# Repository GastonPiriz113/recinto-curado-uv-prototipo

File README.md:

# recinto-curado-uv-prototipo
Firmware y documentación del prototipo de recinto de curado

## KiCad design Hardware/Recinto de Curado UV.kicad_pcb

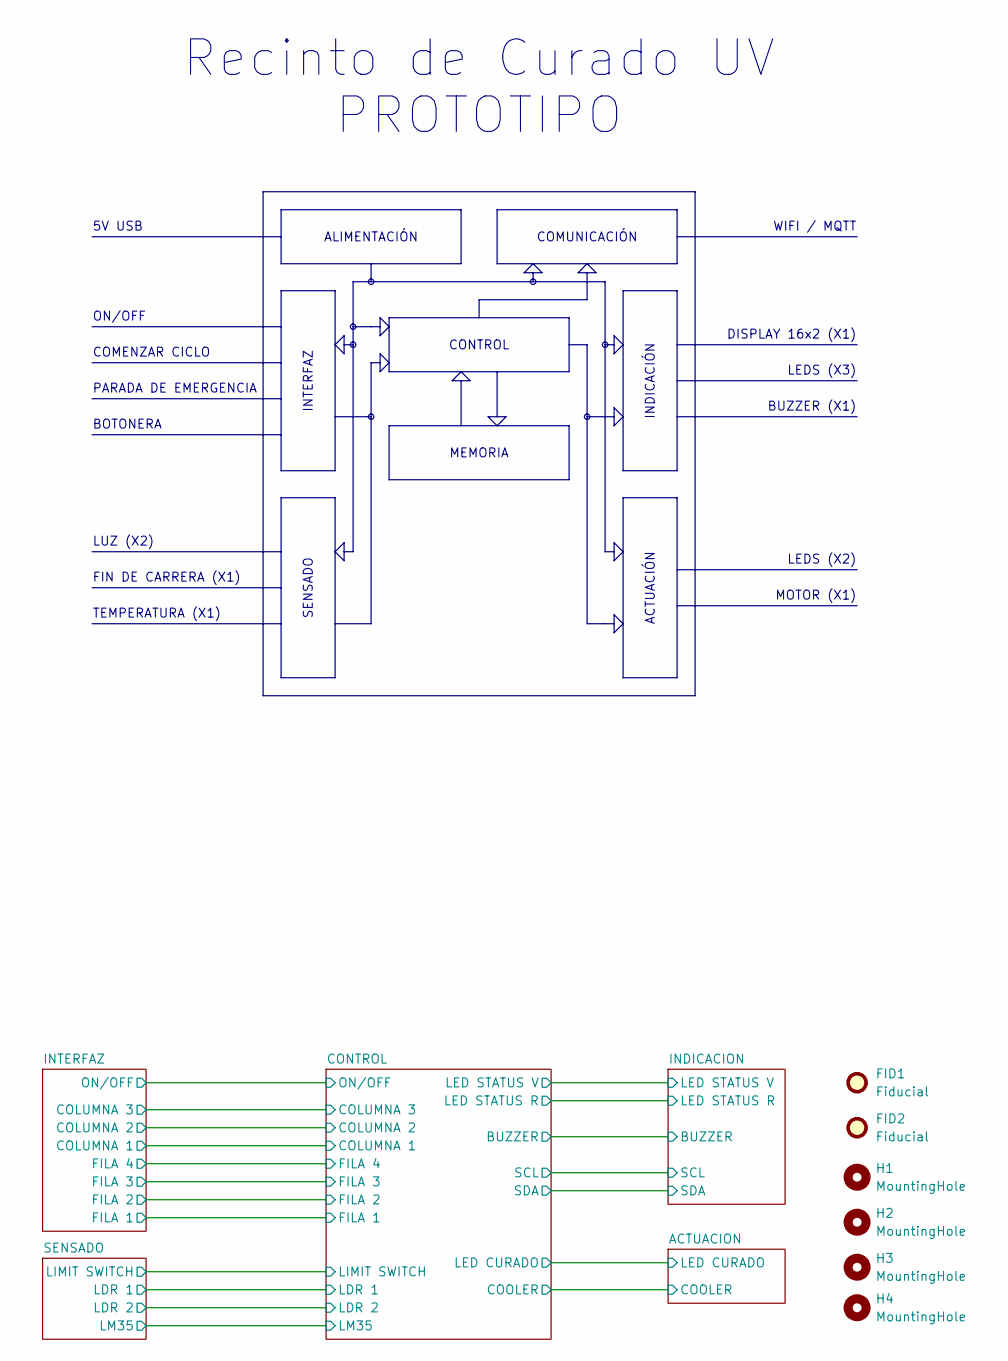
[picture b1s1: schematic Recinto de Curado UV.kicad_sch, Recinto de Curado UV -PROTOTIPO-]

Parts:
FID1, FID2: Fiducial; Fiducial_0.5mm_Mask1.5mm
H1, H2, H3, H4: MountingHole; MountingHole_3.2mm_M3_ISO7380

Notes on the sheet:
DISPLAY 16x2 (X1)
BUZZER (X1)
LEDS (X2)
ON/OFF
WIFI / MQTT
LUZ (X2)
PARADA DE EMERGENCIA
BOTONERA
MOTOR (X1)
COMENZAR CICLO
Recinto de Curado UV PROTOTIPO
LEDS (X3)
FIN DE CARRERA (X1)
5V USB
TEMPERATURA (X1)
MEMORIA
COMUNICACIÓN
SENSADO
INDICACIÓN
ALIMENTACIÓN
ACTUACIÓN
CONTROL
INTERFAZ

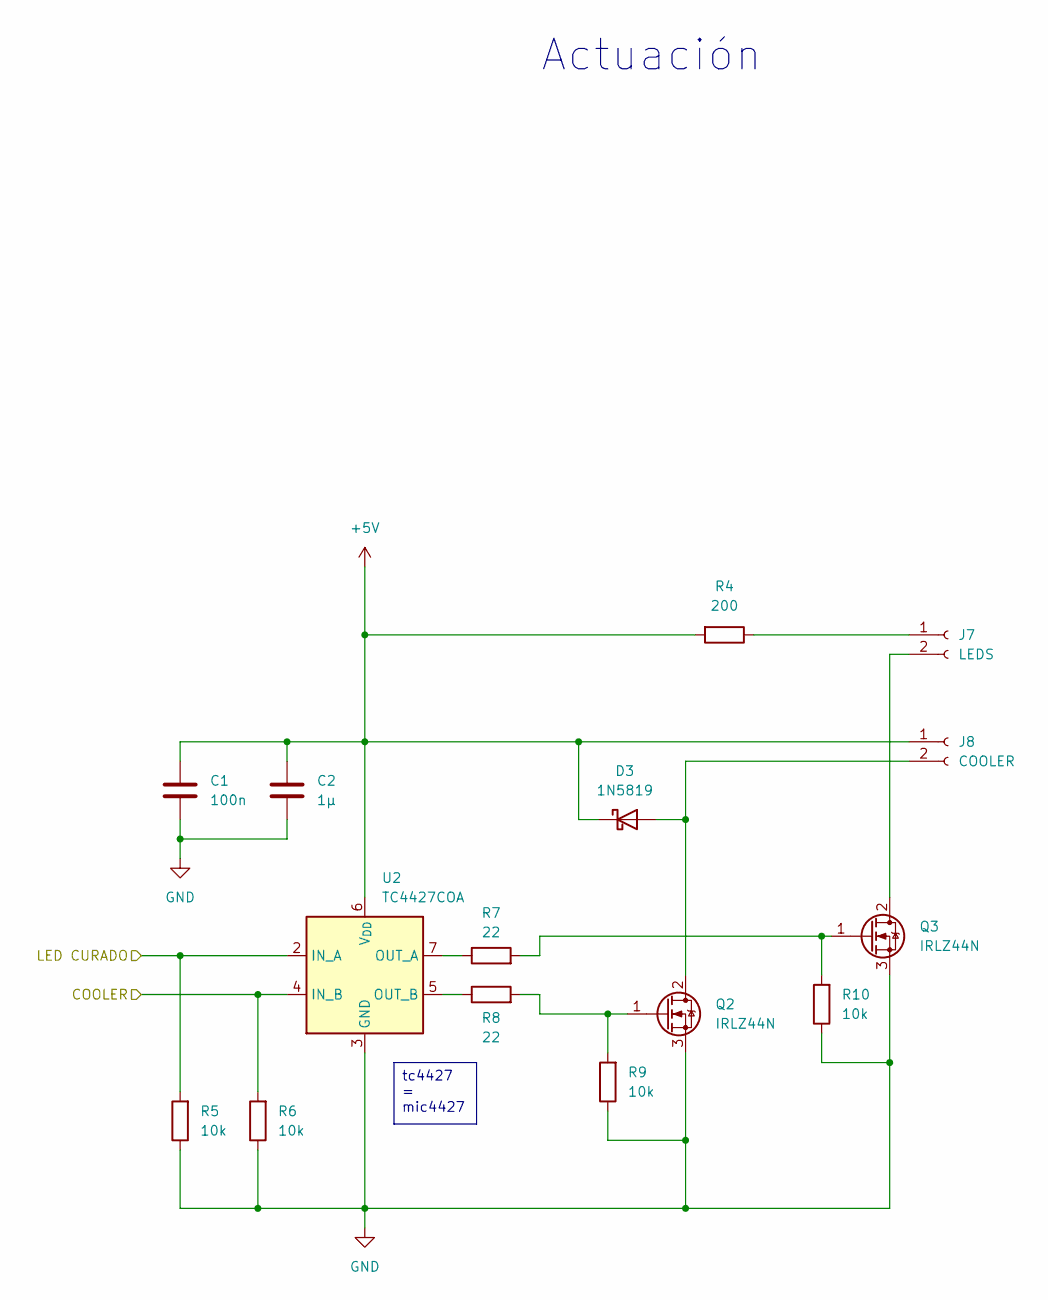
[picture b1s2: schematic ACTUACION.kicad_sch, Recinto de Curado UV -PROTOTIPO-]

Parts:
C1: 100n; C_Disc_D5.0mm_W2.5mm_P2.50mm
C2: 1µ; C_Disc_D5.0mm_W2.5mm_P2.50mm
D3: 1N5819; D_DO-41_SOD81_P10.16mm_Horizontal
J7: LEDS; PinHeader_1x02_P2.54mm_Vertical
J8: COOLER; PinHeader_1x02_P2.54mm_Vertical
Q2, Q3: IRLZ44N; TO-220-3_Horizontal_TabDown
R4: 200; R_Axial_DIN0207_L6.3mm_D2.5mm_P7.62mm_Horizontal
R5, R6, R9, R10: 10k; R_Axial_DIN0207_L6.3mm_D2.5mm_P7.62mm_Horizontal
R7, R8: 22; R_Axial_DIN0207_L6.3mm_D2.5mm_P7.62mm_Horizontal
U2: TC4427COA; SOIC-8_3.9x4.9mm_P1.27mm

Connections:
+5V: C1.1, C2.1, D3.1 (K), J8.1, R4.2, U2.6 (V_{DD}); also elsewhere on the board
/PROTOTIPO/ACTUACION/COOLER: R6.2, U2.4 (IN_B); also elsewhere on the board
/PROTOTIPO/ACTUACION/LED CURADO: R5.2, U2.2 (IN_A); also elsewhere on the board
GND: C1.2, C2.2, Q2.3 (S), Q3.3 (S), R5.1, R6.1, R9.1, R10.1, U2.3 (GND); also elsewhere on the board
unnamed: D3.2 (A), J8.2, Q2.2 (D)
unnamed: J7.1, R4.1
unnamed: J7.2, Q3.2 (D)
unnamed: Q2.1 (G), R8.2, R9.2
unnamed: Q3.1 (G), R7.2, R10.2
unnamed: R7.1, U2.7 (OUT_A)
unnamed: R8.1, U2.5 (OUT_B)

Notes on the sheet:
Actuación
tc4427 = mic4427

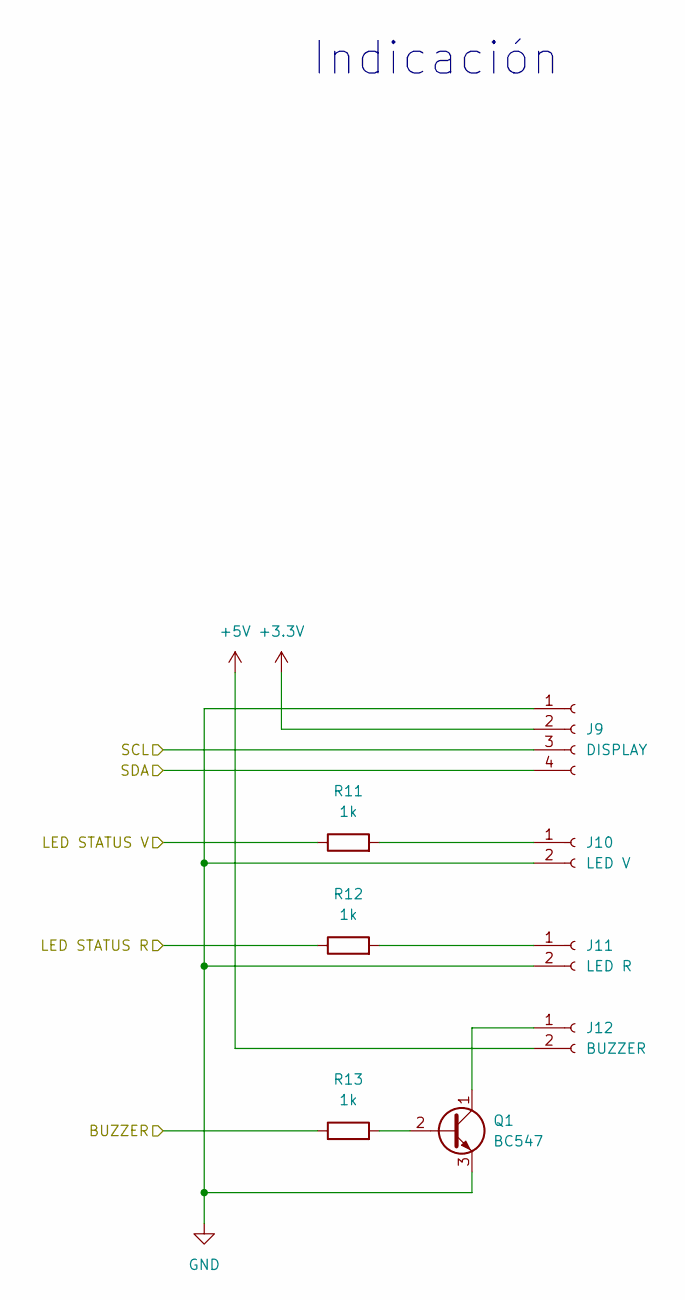
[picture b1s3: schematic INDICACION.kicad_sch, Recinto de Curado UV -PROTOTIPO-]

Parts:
J9: DISPLAY; PinSocket_1x04_P2.54mm_Vertical
J10: LED V; PinSocket_1x02_P2.54mm_Vertical
J11: LED R; PinSocket_1x02_P2.54mm_Vertical
J12: BUZZER; PinSocket_1x02_P2.54mm_Vertical
Q1: BC547; TO-92_Inline
R11, R12, R13: 1k; R_Axial_DIN0207_L6.3mm_D2.5mm_P7.62mm_Horizontal

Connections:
+3.3V: J9.2; also elsewhere on the board
+5V: J12.2; also elsewhere on the board
/PROTOTIPO/CONTROL/BUZZER: R13.1; also elsewhere on the board
/PROTOTIPO/CONTROL/LED STATUS R: R12.1; also elsewhere on the board
/PROTOTIPO/CONTROL/LED STATUS V: R11.1; also elsewhere on the board
/PROTOTIPO/CONTROL/SCL: J9.3; also elsewhere on the board
/PROTOTIPO/CONTROL/SDA: J9.4; also elsewhere on the board
GND: J9.1, J10.2, J11.2, Q1.3 (E); also elsewhere on the board
unnamed: J10.1, R11.2
unnamed: J11.1, R12.2
unnamed: J12.1, Q1.1 (C)
unnamed: Q1.2 (B), R13.2

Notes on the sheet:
Indicación

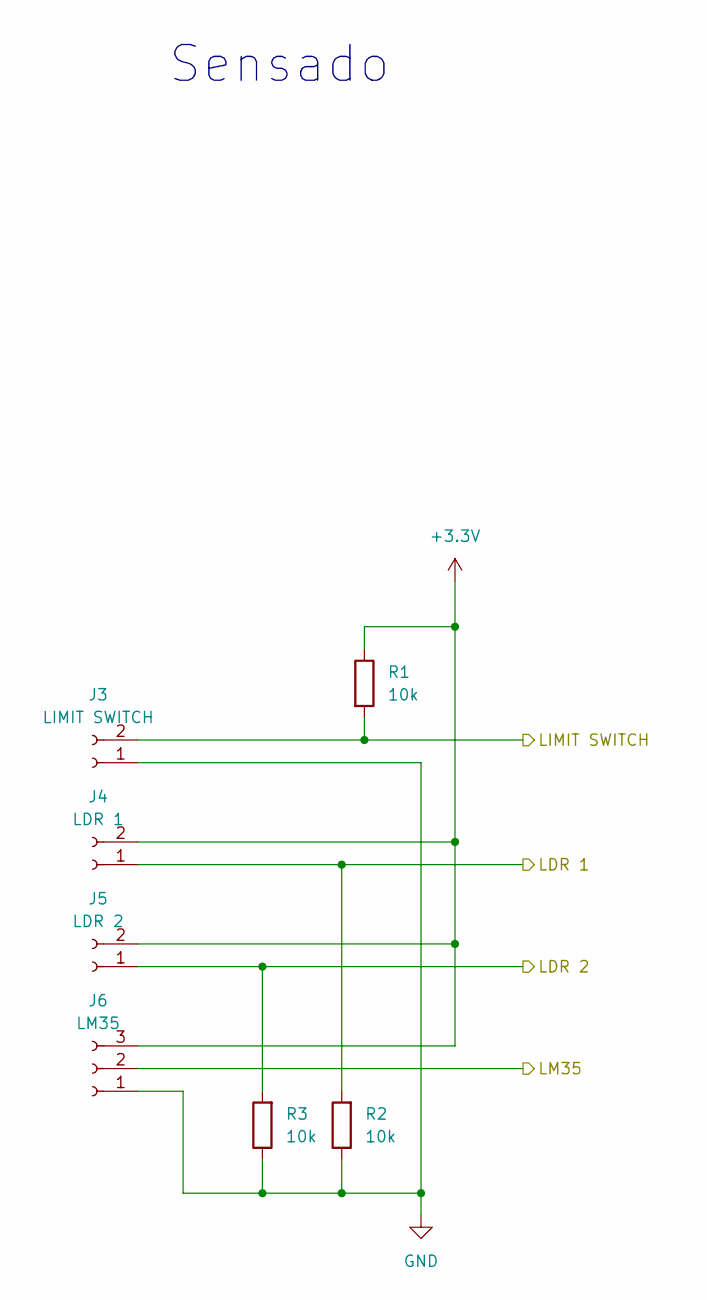
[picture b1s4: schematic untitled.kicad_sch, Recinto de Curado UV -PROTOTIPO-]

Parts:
J3: LIMIT SWITCH; PinHeader_1x02_P2.54mm_Vertical
J4: LDR 1; PinHeader_1x02_P2.54mm_Vertical
J5: LDR 2; PinHeader_1x02_P2.54mm_Vertical
J6: LM35; PinHeader_1x03_P2.54mm_Vertical
R1, R2, R3: 10k; R_Axial_DIN0207_L6.3mm_D2.5mm_P7.62mm_Horizontal

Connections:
+3.3V: J4.2, J5.2, J6.3, R1.1; also elsewhere on the board
/PROTOTIPO/CONTROL/LDR 1: J4.1, R2.2; also elsewhere on the board
/PROTOTIPO/CONTROL/LDR 2: J5.1, R3.2; also elsewhere on the board
/PROTOTIPO/CONTROL/LIMIT SWITCH: J3.2, R1.2; also elsewhere on the board
/PROTOTIPO/CONTROL/LM35: J6.2; also elsewhere on the board
GND: J3.1, J6.1, R2.1, R3.1; also elsewhere on the board

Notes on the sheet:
Sensado

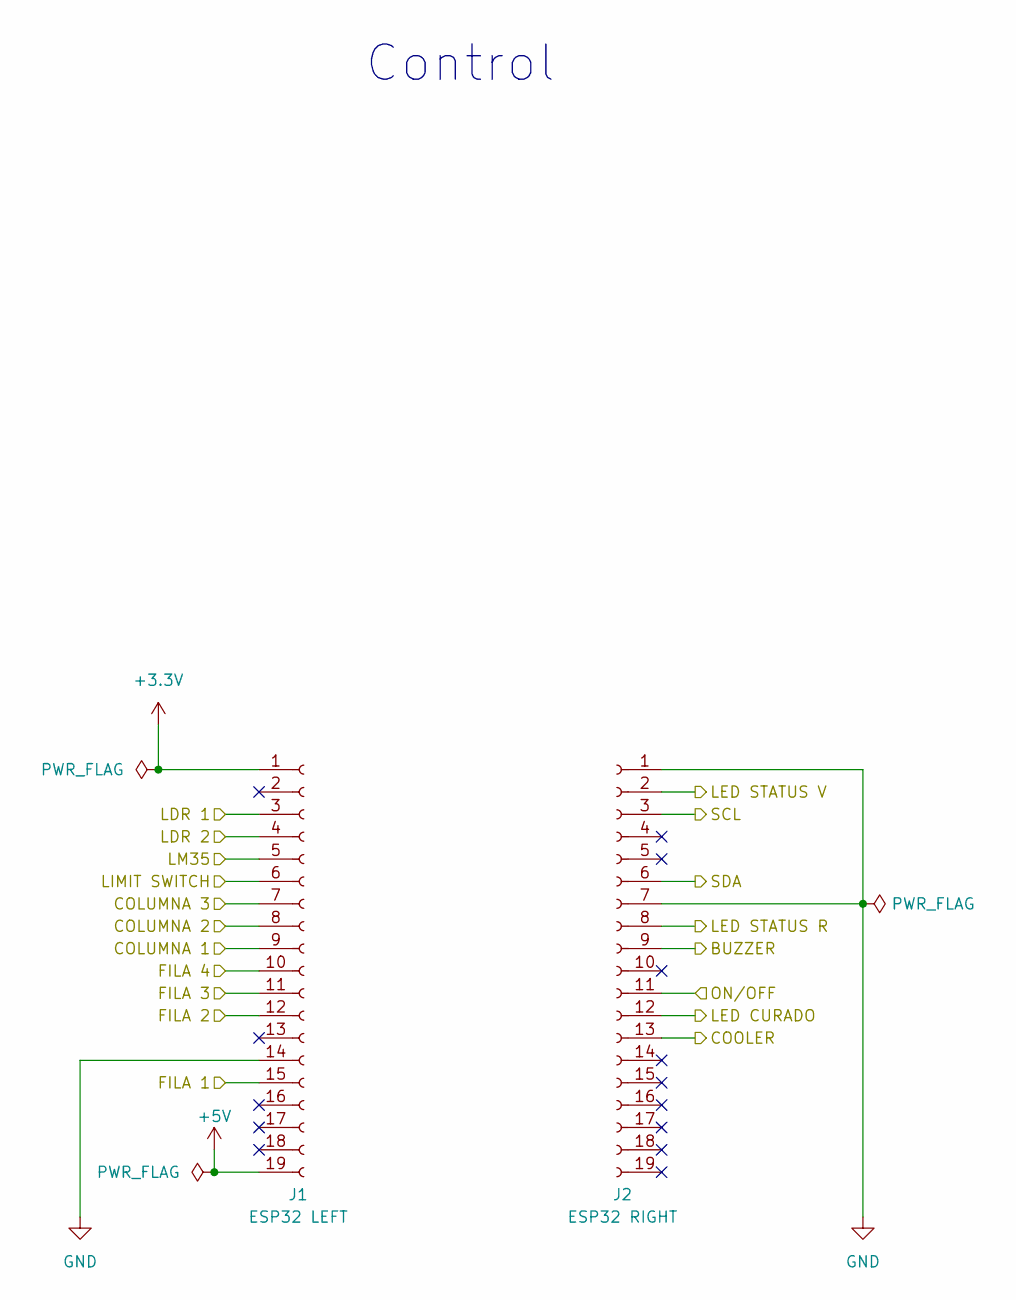
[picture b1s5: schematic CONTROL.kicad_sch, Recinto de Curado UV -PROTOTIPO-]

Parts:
J1: ESP32 LEFT; PinSocket_1x19_P2.54mm_Vertical
J2: ESP32 RIGHT; PinSocket_1x19_P2.54mm_Vertical

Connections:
+3.3V: J1.1; also elsewhere on the board
+5V: J1.19; also elsewhere on the board
/PROTOTIPO/ACTUACION/COOLER: J2.13; also elsewhere on the board
/PROTOTIPO/ACTUACION/LED CURADO: J2.12; also elsewhere on the board
/PROTOTIPO/CONTROL/BUZZER: J2.9; also elsewhere on the board
/PROTOTIPO/CONTROL/COLUMNA 1: J1.9; also elsewhere on the board
/PROTOTIPO/CONTROL/COLUMNA 2: J1.8; also elsewhere on the board
/PROTOTIPO/CONTROL/COLUMNA 3: J1.7; also elsewhere on the board
/PROTOTIPO/CONTROL/FILA 1: J1.15; also elsewhere on the board
/PROTOTIPO/CONTROL/FILA 2: J1.12; also elsewhere on the board
/PROTOTIPO/CONTROL/FILA 3: J1.11; also elsewhere on the board
/PROTOTIPO/CONTROL/FILA 4: J1.10; also elsewhere on the board
/PROTOTIPO/CONTROL/LDR 1: J1.3; also elsewhere on the board
/PROTOTIPO/CONTROL/LDR 2: J1.4; also elsewhere on the board
/PROTOTIPO/CONTROL/LED STATUS R: J2.8; also elsewhere on the board
/PROTOTIPO/CONTROL/LED STATUS V: J2.2; also elsewhere on the board
/PROTOTIPO/CONTROL/LIMIT SWITCH: J1.6; also elsewhere on the board
/PROTOTIPO/CONTROL/LM35: J1.5; also elsewhere on the board
/PROTOTIPO/CONTROL/ON/OFF: J2.11; also elsewhere on the board
/PROTOTIPO/CONTROL/SCL: J2.3; also elsewhere on the board
/PROTOTIPO/CONTROL/SDA: J2.6; also elsewhere on the board
GND: J1.14, J2.1, J2.7; also elsewhere on the board

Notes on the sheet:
Control

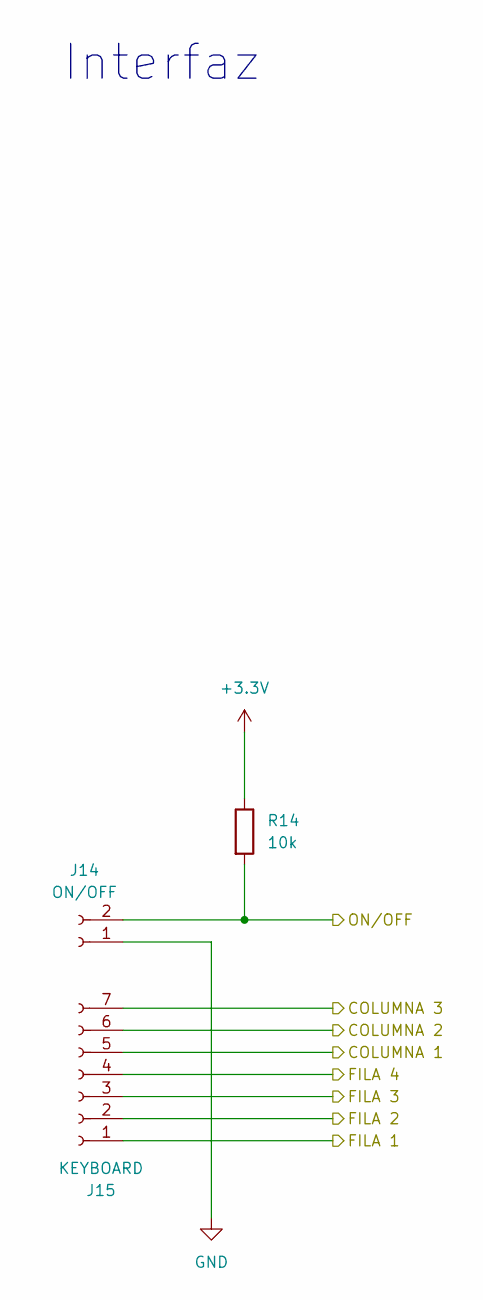
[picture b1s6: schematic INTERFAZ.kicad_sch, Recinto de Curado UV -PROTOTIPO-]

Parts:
J14: ON/OFF; PinSocket_1x02_P2.54mm_Vertical
J15: KEYBOARD; PinSocket_1x07_P2.54mm_Vertical
R14: 10k; R_Axial_DIN0207_L6.3mm_D2.5mm_P7.62mm_Horizontal

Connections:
+3.3V: R14.1; also elsewhere on the board
/PROTOTIPO/CONTROL/COLUMNA 1: J15.5; also elsewhere on the board
/PROTOTIPO/CONTROL/COLUMNA 2: J15.6; also elsewhere on the board
/PROTOTIPO/CONTROL/COLUMNA 3: J15.7; also elsewhere on the board
/PROTOTIPO/CONTROL/FILA 1: J15.1; also elsewhere on the board
/PROTOTIPO/CONTROL/FILA 2: J15.2; also elsewhere on the board
/PROTOTIPO/CONTROL/FILA 3: J15.3; also elsewhere on the board
/PROTOTIPO/CONTROL/FILA 4: J15.4; also elsewhere on the board
/PROTOTIPO/CONTROL/ON/OFF: J14.2, R14.2; also elsewhere on the board
GND: J14.1; also elsewhere on the board

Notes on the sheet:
Interfaz

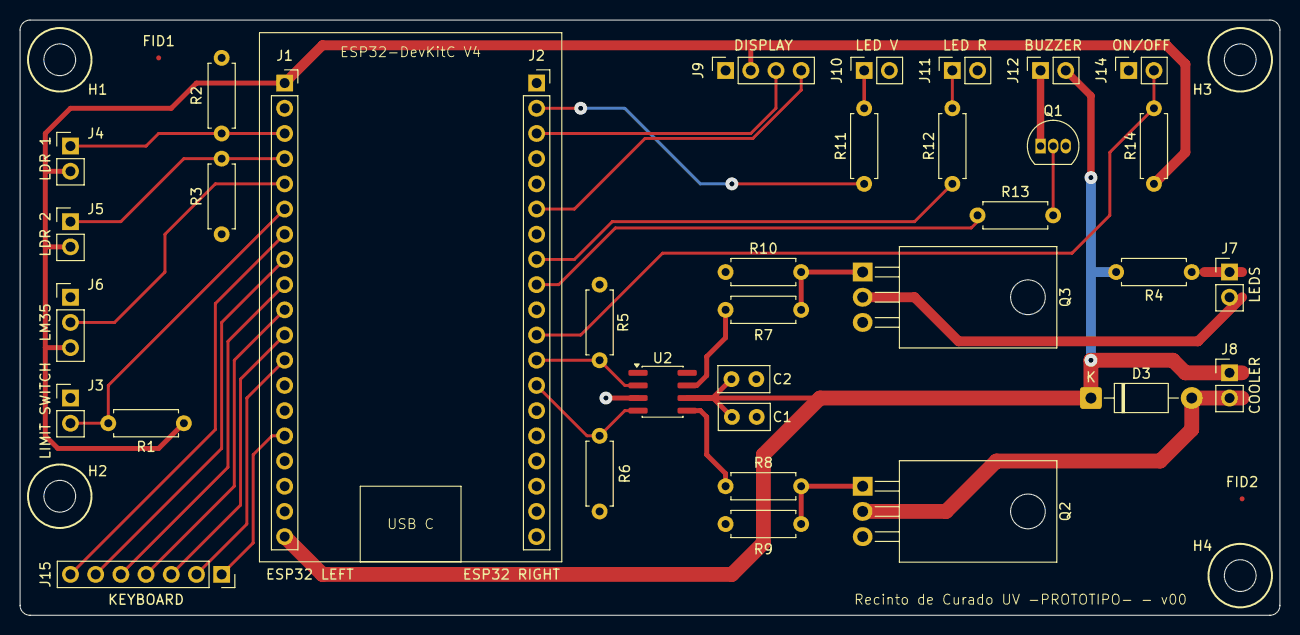
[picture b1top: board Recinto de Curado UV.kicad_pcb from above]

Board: 2 copper layers, 127.0 x 60.0 mm, 41 parts (0 on the bottom side), 33 nets.
